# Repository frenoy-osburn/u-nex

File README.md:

u-nex
=====

Design files, sample sketches, user guides for u-nex.

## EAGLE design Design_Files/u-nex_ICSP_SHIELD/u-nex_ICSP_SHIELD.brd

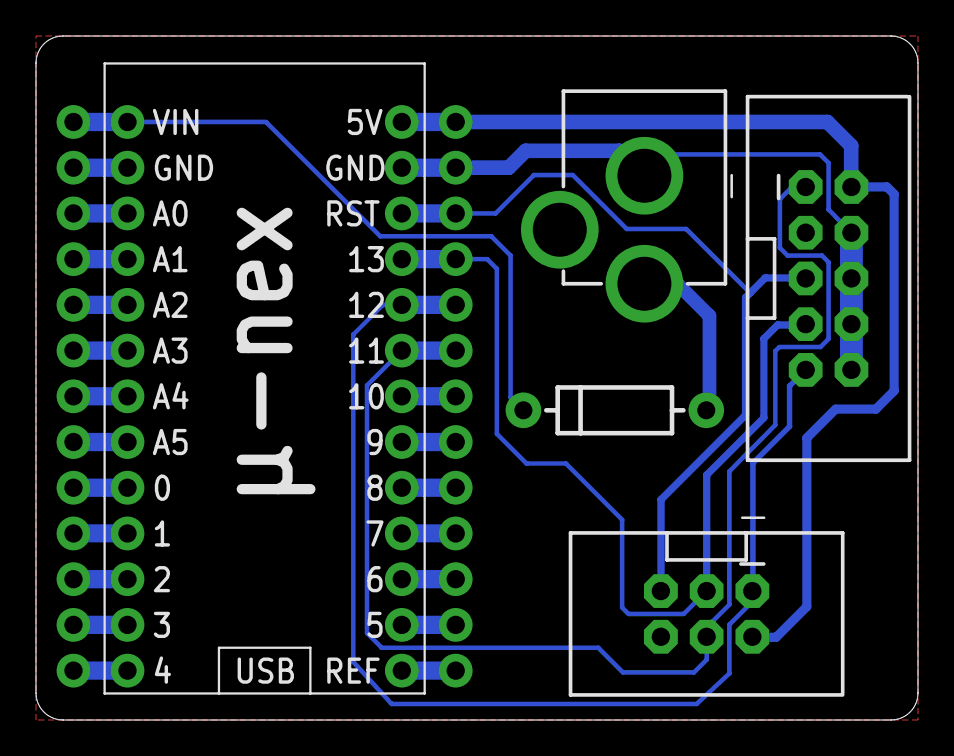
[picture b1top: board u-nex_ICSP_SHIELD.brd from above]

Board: 2 copper layers, 49.0 x 38.0 mm, 7 parts (0 on the bottom side), 26 nets.

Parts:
D1: DIODE-1N4001
J2: POWER_JACKPTH; POWER_JACK_PTH
U$1, U$4: M13; 1X13
U$2: AVR_SPI_PROG2PTH2; 2X5-SHROUDED
U$6: AVR_ICSP_6; 2X3_SHROUDED
U$10: U-NEX

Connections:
5V0: U$2.2, U$4.13, U$6.2, U$10.5V
A0: U$1.11, U$10.A0
A1: U$1.10, U$10.A1
A2: U$1.9, U$10.A2
A3: U$1.8, U$10.A3
A4: U$1.7, U$10.A4
A5: U$1.6, U$10.A5
D0: U$1.5, U$10.0
D1: U$1.4, U$10.1
D2: U$1.3, U$10.2
D3: U$1.2, U$10.3
D4: U$1.1, U$10.4
D5: U$4.2, U$10.5
D6: U$4.3, U$10.6
D7: U$4.4, U$10.7
D8: U$4.5, U$10.8
D9: U$4.6, U$10.9
D10: U$4.7, U$10.10
GND: J2.GND, U$1.12, U$2.4, U$2.6, U$2.8, U$2.10, U$4.12, U$6.6, U$10.GND, U$10.GND2
MISO: U$2.9, U$4.9, U$6.1, U$10.12
MOSI: U$2.1, U$4.8, U$6.4, U$10.11
unnamed: D1.A, J2.PWR
REF: U$4.1, U$10.REF
RST: U$2.5, U$4.11, U$6.5, U$10.RST
SCK: U$2.7, U$4.10, U$6.3, U$10.13
VIN: D1.C, U$1.13, U$10.VIN

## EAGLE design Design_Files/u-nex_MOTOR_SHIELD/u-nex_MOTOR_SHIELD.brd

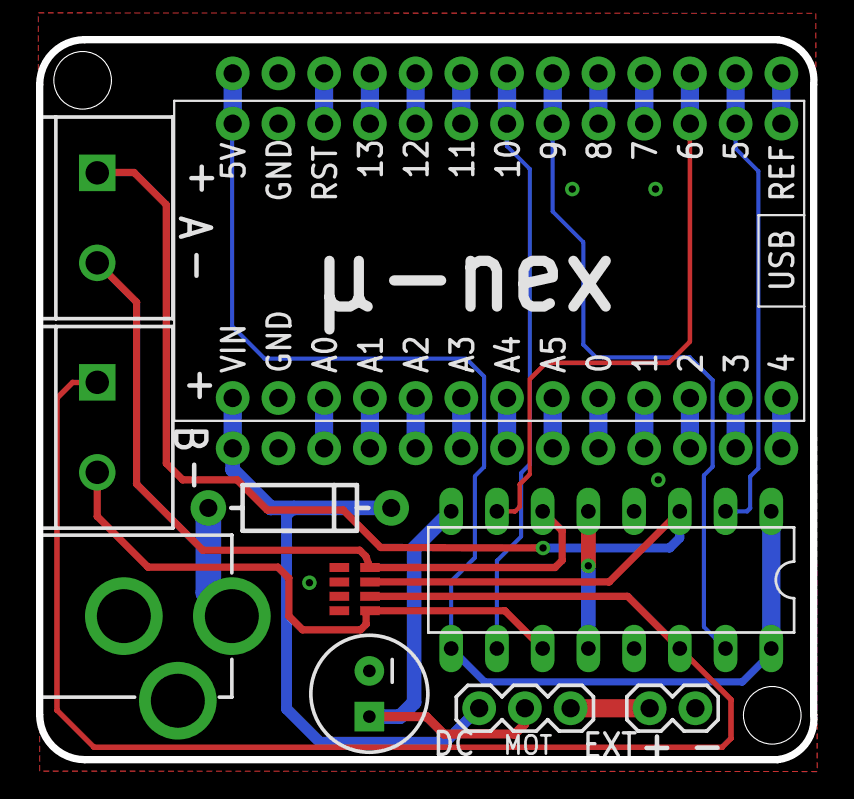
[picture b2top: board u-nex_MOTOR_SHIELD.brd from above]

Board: 2 copper layers, 43.0 x 40.0 mm, 12 parts (0 on the bottom side), 32 nets.

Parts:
C2: 100uF; CPOL-RADIAL-100UF-25V
D1: DIODE-1N4001
IC1: L293D; DIL16
J2: POWER_JACKPTH; POWER_JACK_PTH
JP1: M02PTH; 1X02
JP2: 1X03
JP4, JP5: M025MM; SCREWTERMINAL-5MM-2
U$1, U$4: M13; 1X13
U$2: 0.1uF; 0603_ARV
U$10: U-NEX

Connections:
5V0: IC1.1, IC1.9, IC1.16, U$1.13, U$10.5V
A0: U$4.11, U$10.A0
A1: U$4.10, U$10.A1
A2: U$4.9, U$10.A2
A3: U$4.8, U$10.A3
A4: U$4.7, U$10.A4
A5: U$4.6, U$10.A5
D0: U$4.5, U$10.0
D1: U$4.4, U$10.1
D2: U$4.3, U$10.2
D3: U$4.2, U$10.3
D4: U$4.1, U$10.4
D7: U$1.4, U$10.7
D8: U$1.5, U$10.8
D11: U$1.8, U$10.11
D12: U$1.9, U$10.12
D13: U$1.10, U$10.13
GND: C2.2, IC1.4, IC1.5, IC1.12, IC1.13, J2.GND, JP1.2, U$1.12, U$2.5, U$2.6, U$2.7, U$2.8, U$4.12, U$10.GND, U$10.GND2
MOT_A_+: IC1.3, JP4.1, U$2.3
MOT_A_-: IC1.6, JP4.2, U$2.4
MOT_B_+: IC1.14, JP5.1, U$2.2
MOT_B_-: IC1.11, JP5.2, U$2.1
PWM_A_+: IC1.2, U$1.2, U$10.5
PWM_A_-: IC1.7, U$1.3, U$10.6
PWM_B_+: IC1.15, U$1.6, U$10.9
PWM_B_-: IC1.10, U$1.7, U$10.10
RAW_PWR: D1.A, J2.PWR
REF: U$1.1, U$10.REF
RST: U$1.11, U$10.RST
VEXT: JP1.1, JP2.1
VIN: D1.C, JP2.3, U$4.13, U$10.VIN
VMOT: C2.1, IC1.8, JP2.2

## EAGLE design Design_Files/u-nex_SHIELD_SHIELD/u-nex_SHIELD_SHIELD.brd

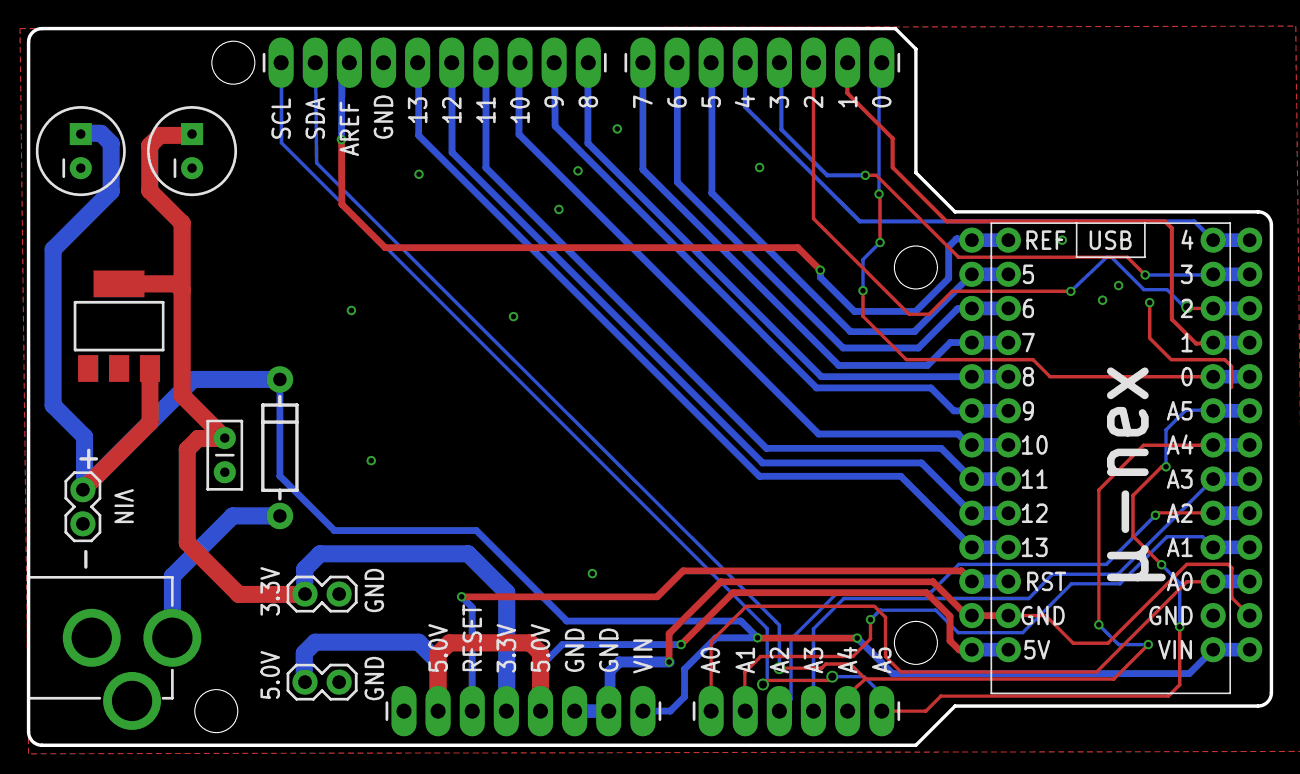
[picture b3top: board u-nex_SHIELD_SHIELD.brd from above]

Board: 2 copper layers, 92.5 x 53.3 mm, 16 parts (0 on the bottom side), 27 nets.

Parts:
C1: 47uF; CPOL-RADIAL-100UF-25V
C2: 1uF; CPOL-RADIAL-100UF-25V
C3: 0.1uF; CAP-PTH-SMALLEZ
D1: DIODE-1N4001
IC2: LD117AS33TR; SOT223
J2: POWER_JACKPTH; POWER_JACK_PTH
JP1, JP4, JP7: M02PTH; 1X02
JP2, JP3: 1X08_LONGPADS
JP6: 1X06_LONGPADS
U$2, U$3: M13; 1X13
U$8: M1X10_LONGPADS; 1X10_LONGPADS
U$10: U-NEX

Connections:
3V3: C1.1, C3.1, IC2.4, JP1.1, JP3.4
5V0: JP3.2, JP3.5, JP4.1, U$3.13, U$10.5V
A0: JP6.1, U$2.11, U$10.A0
A1: JP6.2, U$2.10, U$10.A1
A2: JP6.3, U$2.9, U$10.A2
A3: JP6.4, U$2.8, U$10.A3
A4/SDA: JP6.5, U$2.7, U$8.9, U$10.A4
A5/SCL: JP6.6, U$2.6, U$8.10, U$10.A5
AREF: U$3.1, U$8.8, U$10.REF
D0/RX: JP2.1, U$2.5, U$10.0
D1/TX: JP2.2, U$2.4, U$10.1
D2: JP2.3, U$2.3, U$10.2
D3: JP2.4, U$2.2, U$10.3
D4: JP2.5, U$2.1, U$10.4
D5: JP2.6, U$3.2, U$10.5
D6: JP2.7, U$3.3, U$10.6
D7: JP2.8, U$3.4, U$10.7
GND: C1.2, C2.2, C3.2, IC2.1, J2.GND, JP1.2, JP3.6, JP3.7, JP4.2, JP7.2, U$2.12, U$3.12, U$8.7, U$10.GND, U$10.GND2
IO8: U$3.5, U$8.1, U$10.8
IO9: U$3.6, U$8.2, U$10.9
IO10: U$3.7, U$8.3, U$10.10
IO11: U$3.8, U$8.4, U$10.11
IO12: U$3.9, U$8.5, U$10.12
IO13: U$3.10, U$8.6, U$10.13
RAW_PWR: D1.A, J2.PWR
RST: JP3.3, U$3.11, U$10.RST
VIN: C2.1, D1.C, IC2.3, JP3.8, JP7.1, U$2.13, U$10.VIN

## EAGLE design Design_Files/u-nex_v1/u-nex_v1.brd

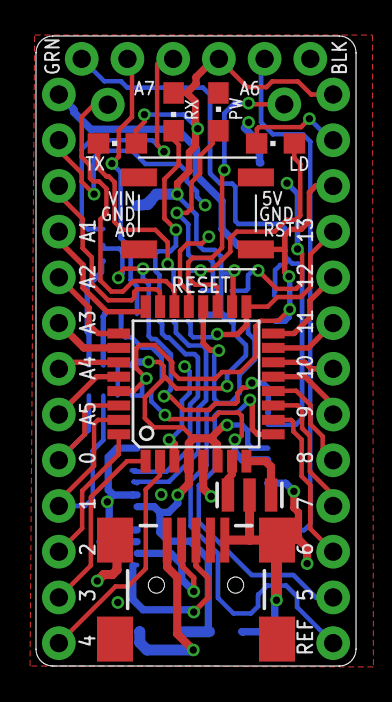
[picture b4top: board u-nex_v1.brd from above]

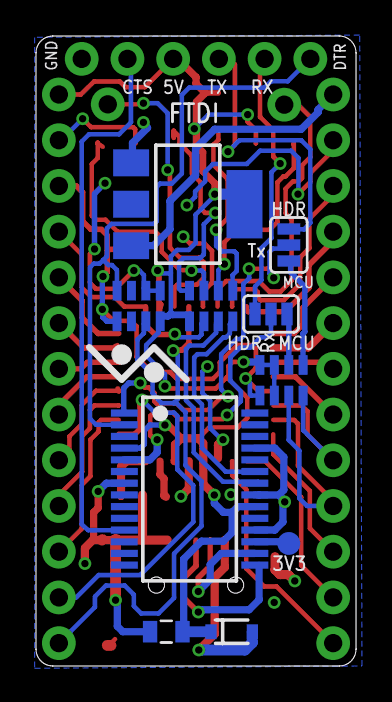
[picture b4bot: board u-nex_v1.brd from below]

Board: 2 copper layers, 17.8 x 35.0 mm, 23 parts (10 on the bottom side), 47 nets.

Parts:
C1: 0805
D1: SOD-323
IC1: FT232RL; SSOP28
IC2: LD117AS50TR; SOT223
JP1, JP2: 1X01_CLEAN
JP3, JP6: M13; 1X13
LED: CHIP; CHIPLED0805
PWR: RED; CHIPLED0805
R1: 1K; 0603_ARV
R2: 330; 0603_ARV
RX_LED: CHIPLED0805_SLIM; CHIPLED0805
SJ1, SJ2: SJ_3
TP1: TPB1,27; B1,27
TX_LED: CHIPLED0805_SLIM; CHIPLED0805
U4: ATMEGA328P; TQFP32-08
U$1: SWITCH_6.8X6.2
U$4: 0.1uF; 0603_ARV
U$5: 1X06_NO_MARKS; 1X06_CLEAN
U$9: USB-MINIB-5PIN; USB-MINIB
Y2: 16MHz; RESONATOR_SMD

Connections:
3V3: IC1.17, TP1.TP
5V0: C1.1, D1.1, IC1.4, IC1.20, IC2.4, JP6.13, R1.2, R1.7, R1.8, R2.1, RX_LED.A, TX_LED.A, U4.4, U4.6, U4.18, U$4.4, U$5.4
A0: JP3.11, U4.23
A1: JP3.10, U4.24
A2: JP3.9, U4.25
A3: JP3.8, U4.26
A4: JP3.7, U4.27
A5: JP3.6, U4.28
A6: JP1.1, U4.19
A7: JP2.1, U4.22
AREF: JP6.1, U4.20, U$4.3
CTS: IC1.11, U$5.5
D0: JP3.5, R1.4, U4.30
D1: JP3.4, R1.3, U4.31
D2: JP3.3, U4.32
D3: JP3.2, U4.1
D4: JP3.1, U4.2
D5: JP6.2, U4.9
D6: JP6.3, U4.10
D7: JP6.4, U4.11
D8: JP6.5, U4.12
D9: JP6.6, U4.13
D10: JP6.7, U4.14
D11: JP6.8, U4.15
D12: JP6.9, U4.16
D13: JP6.10, R2.2, U4.17
DTR: IC1.2, U$4.8, U$5.1
FTDI_RX_IN: IC1.5, SJ2.2
FTDI_TX_OUT: IC1.1, SJ1.2
GND: C1.2, IC1.7, IC1.18, IC1.21, IC1.25, IC2.1, JP3.12, JP6.12, LED.C, PWR.C, U4.3, U4.5, U4.21, U$1.1, U$4.5, U$4.6, U$5.6, U$9.GND, U$9.MTN1, U$9.MTN2, U$9.MTN3, U$9.MTN4, Y2.2
HDR_RX: SJ2.3, U$5.2
HDR_TX: SJ1.3, U$5.3
MCU_RESET: JP6.11, R1.1, U4.29, U$1.3, U$4.1
MCU_RX_IN: R1.5, SJ1.1
MCU_TX_OUT: R1.6, SJ2.1
unnamed: LED.A, R2.7
unnamed: R2.5, RX_LED.C
unnamed: R2.6, TX_LED.C
unnamed: IC1.22, R2.3
unnamed: IC1.23, R2.4
unnamed: PWR.A, R2.8
unnamed: U4.7, Y2.1
unnamed: U4.8, Y2.3
USB_DM: IC1.16, U$9.D-
USB_DP: IC1.15, U$9.D+
VIN: IC2.3, JP3.13
VUSB: D1.2, U$9.VBUS

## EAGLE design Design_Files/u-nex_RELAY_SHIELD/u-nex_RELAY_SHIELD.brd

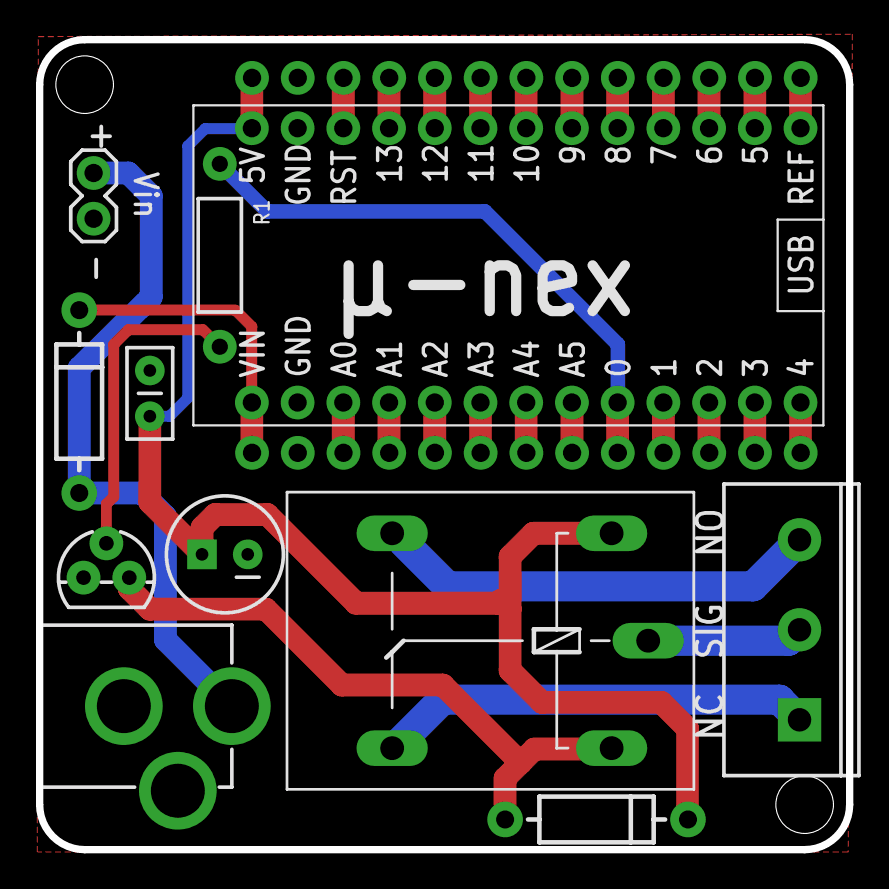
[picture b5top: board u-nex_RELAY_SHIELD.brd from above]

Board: 2 copper layers, 45.0 x 45.0 mm, 13 parts (0 on the bottom side), 31 nets.

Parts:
C1: 0.1uF; CAP-PTH-SMALL2
C2: 100uF; CPOL-RADIAL-100UF-25V
D1, D2: 1N5817; DIODE-1N4001
J2: POWER_JACKPTH; POWER_JACK_PTH
JP1: M02PTH; 1X02
JP2: SCREWTERMINAL-5MM-3
K1: G5L; G5LE
Q1: TO-92
R1: AXIAL-0.4
U$1, U$4: M13; 1X13
U$2: U-NEX

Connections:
5V0: C1.1, C2.1, D2.C, K1.1, U$1.13, U$2.5V
A0: U$2.A0, U$4.11
A1: U$2.A1, U$4.10
A2: U$2.A2, U$4.9
A3: U$2.A3, U$4.8
A4: U$2.A4, U$4.7
A5: U$2.A5, U$4.6
D1: U$2.1, U$4.4
D2: U$2.2, U$4.3
D3: U$2.3, U$4.2
D4: U$2.4, U$4.1
D5: U$1.2, U$2.5
D6: U$1.3, U$2.6
D7: U$1.4, U$2.7
D8: U$1.5, U$2.8
D9: U$1.6, U$2.9
D10: U$1.7, U$2.10
D11: U$1.8, U$2.11
D12: U$1.9, U$2.12
D13: U$1.10, U$2.13
GND: C1.2, C2.2, J2.GND, JP1.2, Q1.1, U$1.12, U$2.GND, U$2.GND2, U$4.12
unnamed: D2.A, K1.2, Q1.3
unnamed: Q1.2, R1.P$2
NC: JP2.1, K1.O
NO: JP2.3, K1.S
RAW_PWR: D1.A, J2.PWR, JP1.1
REF: U$1.1, U$2.REF
RELAY: R1.P$1, U$2.0, U$4.5
RST: U$1.11, U$2.RST
SIG: JP2.2, K1.P
VIN: D1.C, U$2.VIN, U$4.13

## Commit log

2014-05-11 Initial Release
2014-08-01 Added support for ‘board.txt’ update in Mac OSX Fixes #2

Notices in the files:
parts and their libraries:
SparkFun-Connectors: Licensing: CC v3.0 Share-Alike You are welcome to use this library for commercial purposes.
